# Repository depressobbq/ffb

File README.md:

# Force Feedback Board
<br>
This is a 4 channel bass transducer driver for force feedback in sim racing.<br>
<br> the device uses 4 dayton TT25-8 pucks  to add various effects to a sim racing setup, such as engine rpm feel, rough road feel, and several others.

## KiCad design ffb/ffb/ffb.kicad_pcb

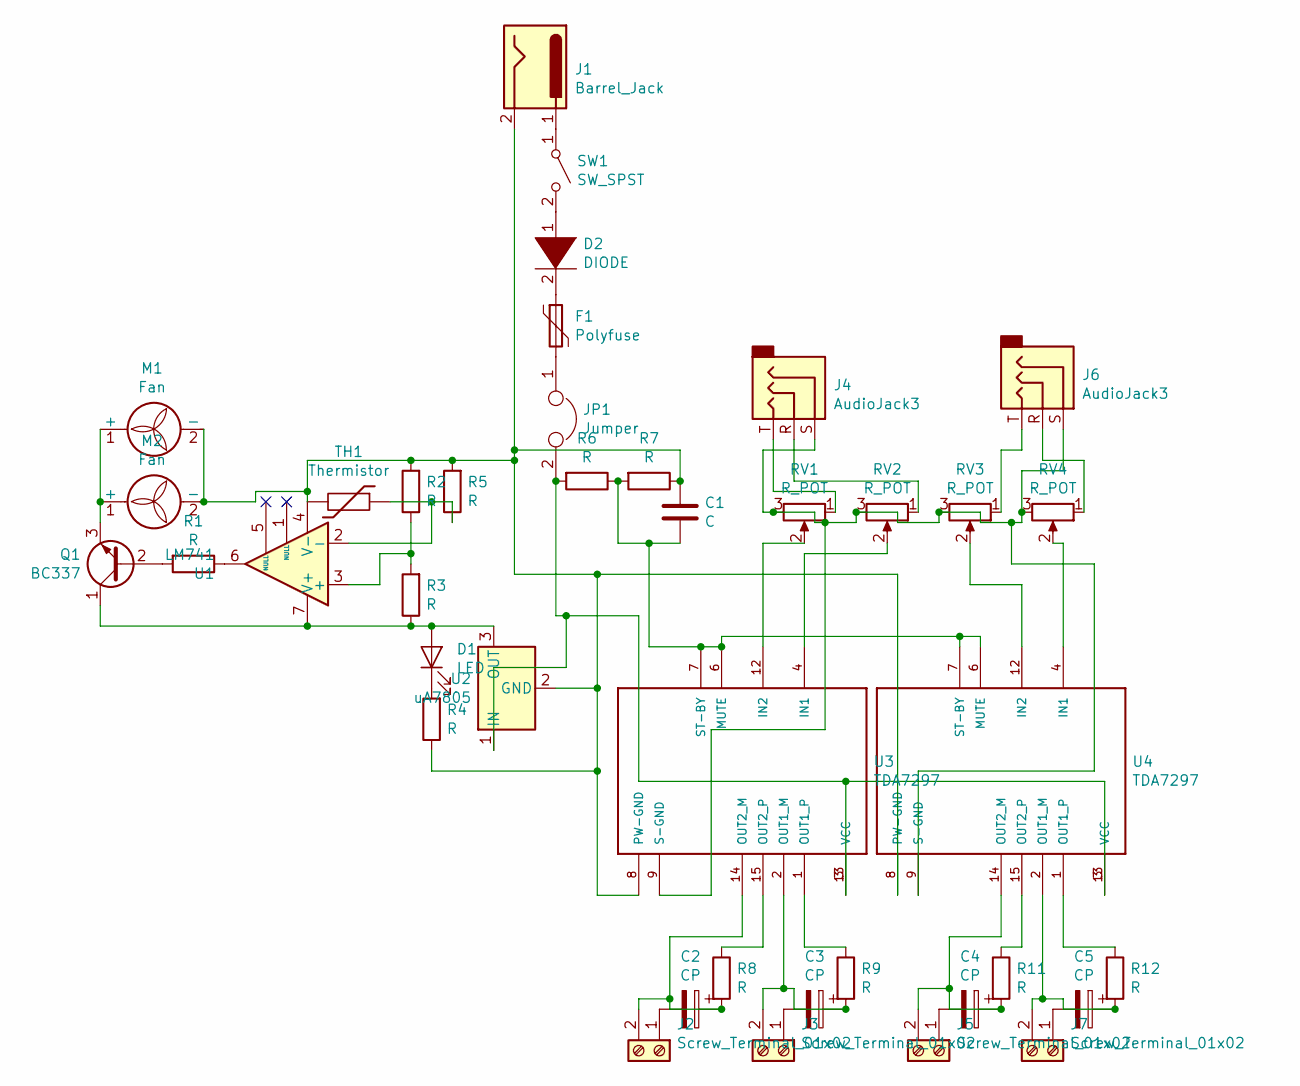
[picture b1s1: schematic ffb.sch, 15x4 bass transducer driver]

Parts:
C1: C; C_Axial_L3.8mm_D2.6mm_P7.50mm_Horizontal
C2, C3, C4, C5: CP; CP_Axial_L10.0mm_D4.5mm_P15.00mm_Horizontal
D1: LED; LED_D5.0mm
D2: DIODE; D_5KPW_P7.62mm_Vertical_AnodeUp
F1: Polyfuse; Fuse_BelFuse_0ZRE0005FF_L8.3mm_W3.8mm
J1: Barrel_Jack; BarrelJack_Horizontal
J2, J3, J5, J7: Screw_Terminal_01x02; TerminalBlock_Altech_AK300-2_P5.00mm
J4, J6: AudioJack3; Jack_3.5mm_CUI_SJ1-3533NG_Horizontal_CircularHoles
JP1: Jumper; SolderJumper-2_P1.3mm_Open_Pad1.0x1.5mm
M1, M2: Fan; Molex_KK-254_AE-6410-03A_1x03_P2.54mm_Vertical
Q1: BC337; TO-92_Inline
R1, R2, R3, R4, R5, R6, R7, R8, R9, R11, R12: R; R_Radial_Power_L11.0mm_W7.0mm_P5.00mm
RV1, RV2, RV3, RV4: R_POT; Potentiometer_Alps_RK163_Single_Horizontal
SW1: SW_SPST; SW_DIP_SPSTx01_Piano_10.8x4.1mm_W7.62mm_P2.54mm
TH1: Thermistor; R_Axial_DIN0204_L3.6mm_D1.6mm_P2.54mm_Vertical
U1: LM741; DIP-8_W7.62mm
U2: uA7805; TO-220-3_Vertical
U3, U4: TDA7297; TO127P2020X500X2100-15

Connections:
unnamed: C1.1, J1.2, M1.2 (-), M2.2 (-), R2.2, R4.1, R5.2, R7.1, TH1.2, U1.4 (V-), U2.2 (GND), U3.8 (PW-GND), U4.8 (PW-GND)
unnamed: C1.2, R6.1, R7.2, U3.6 (MUTE), U3.7 (ST-BY), U4.6 (MUTE), U4.7 (ST-BY)
unnamed: C2.1, J2.2, R8.2, U3.14 (OUT2_M)
unnamed: C2.2, J2.1
unnamed: C3.1, J3.2, R9.2, U3.2 (OUT1_M)
unnamed: C3.2, J3.1
unnamed: C4.1, J5.2, R11.2, U4.14 (OUT2_M)
unnamed: C4.2, J5.1
unnamed: C5.1, J7.2, R12.2, U4.2 (OUT1_M)
unnamed: C5.2, J7.1
unnamed: D1.1 (K), R4.2
unnamed: D1.2 (A), Q1.1 (C), R3.1, U1.7 (V+), U2.3 (OUT)
unnamed: D2.1 (K), SW1.2 (B)
unnamed: D2.2 (A), F1.1
unnamed: F1.2, JP1.1
unnamed: J1.1, SW1.1 (A)
unnamed: J4.R, RV2.1
unnamed: J4.S, J6.S, RV1.3, RV2.3, RV3.3, RV4.3, U3.9 (S-GND), U4.9 (S-GND)
unnamed: J4.T, RV1.1
unnamed: J6.R, RV4.1
unnamed: J6.T, RV3.1
unnamed: JP1.2, R6.2, U2.1 (IN), U3.3 (VCC), U3.13 (VCC), U4.3 (VCC), U4.13 (VCC)
unnamed: M1.1 (+), M2.1 (+), Q1.3 (E)
unnamed: Q1.2 (B), R1.2
unnamed: R1.1, U1.6
unnamed: R2.1, R3.2, U1.3 (+)
unnamed: R5.1, TH1.1, U1.2 (-)
unnamed: R8.1, U3.15 (OUT2_P)
unnamed: R9.1, U3.1 (OUT1_P)
unnamed: R11.1, U4.15 (OUT2_P)
unnamed: R12.1, U4.1 (OUT1_P)
unnamed: RV1.2, U3.12 (IN2)
unnamed: RV2.2, U3.4 (IN1)
unnamed: RV3.2, U4.12 (IN2)
unnamed: RV4.2, U4.4 (IN1)

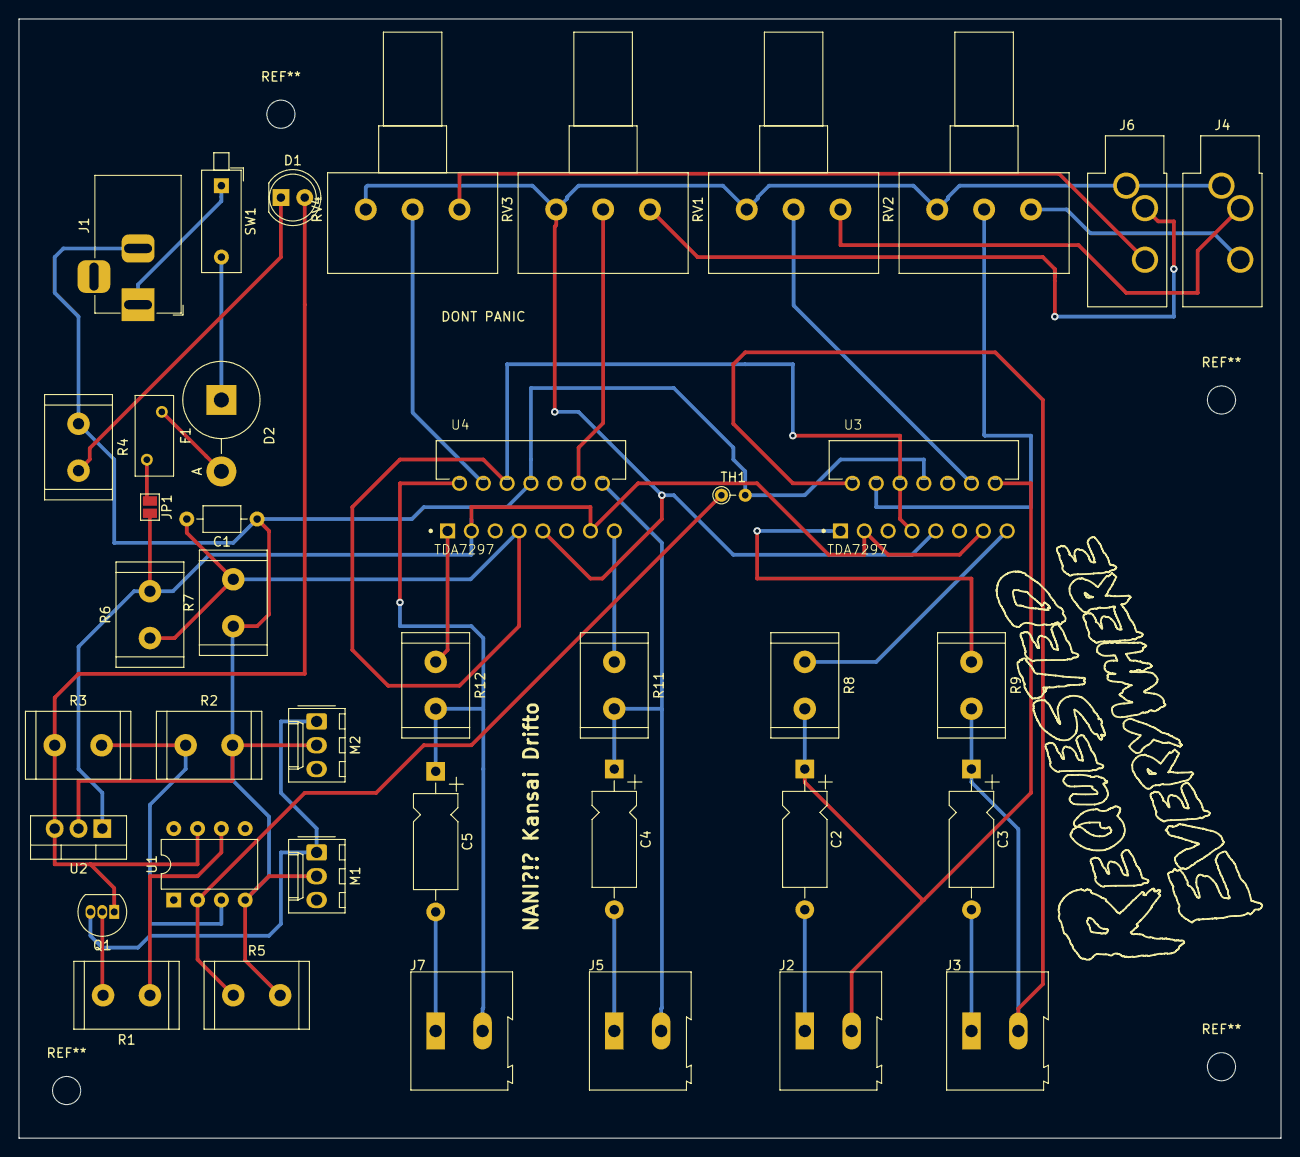
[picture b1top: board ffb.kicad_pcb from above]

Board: 2 copper layers, 134.6 x 119.4 mm, 40 parts (0 on the bottom side), 35 nets.
